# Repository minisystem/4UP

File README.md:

# SYSTEM80 4UP

4HP Eurorack Power. _Under Development_

Hardware design by minisystem: info@system80.net

# LICENSE

cc by-nc-sa
https://creativecommons.org/licenses/by-nc-sa/4.0/

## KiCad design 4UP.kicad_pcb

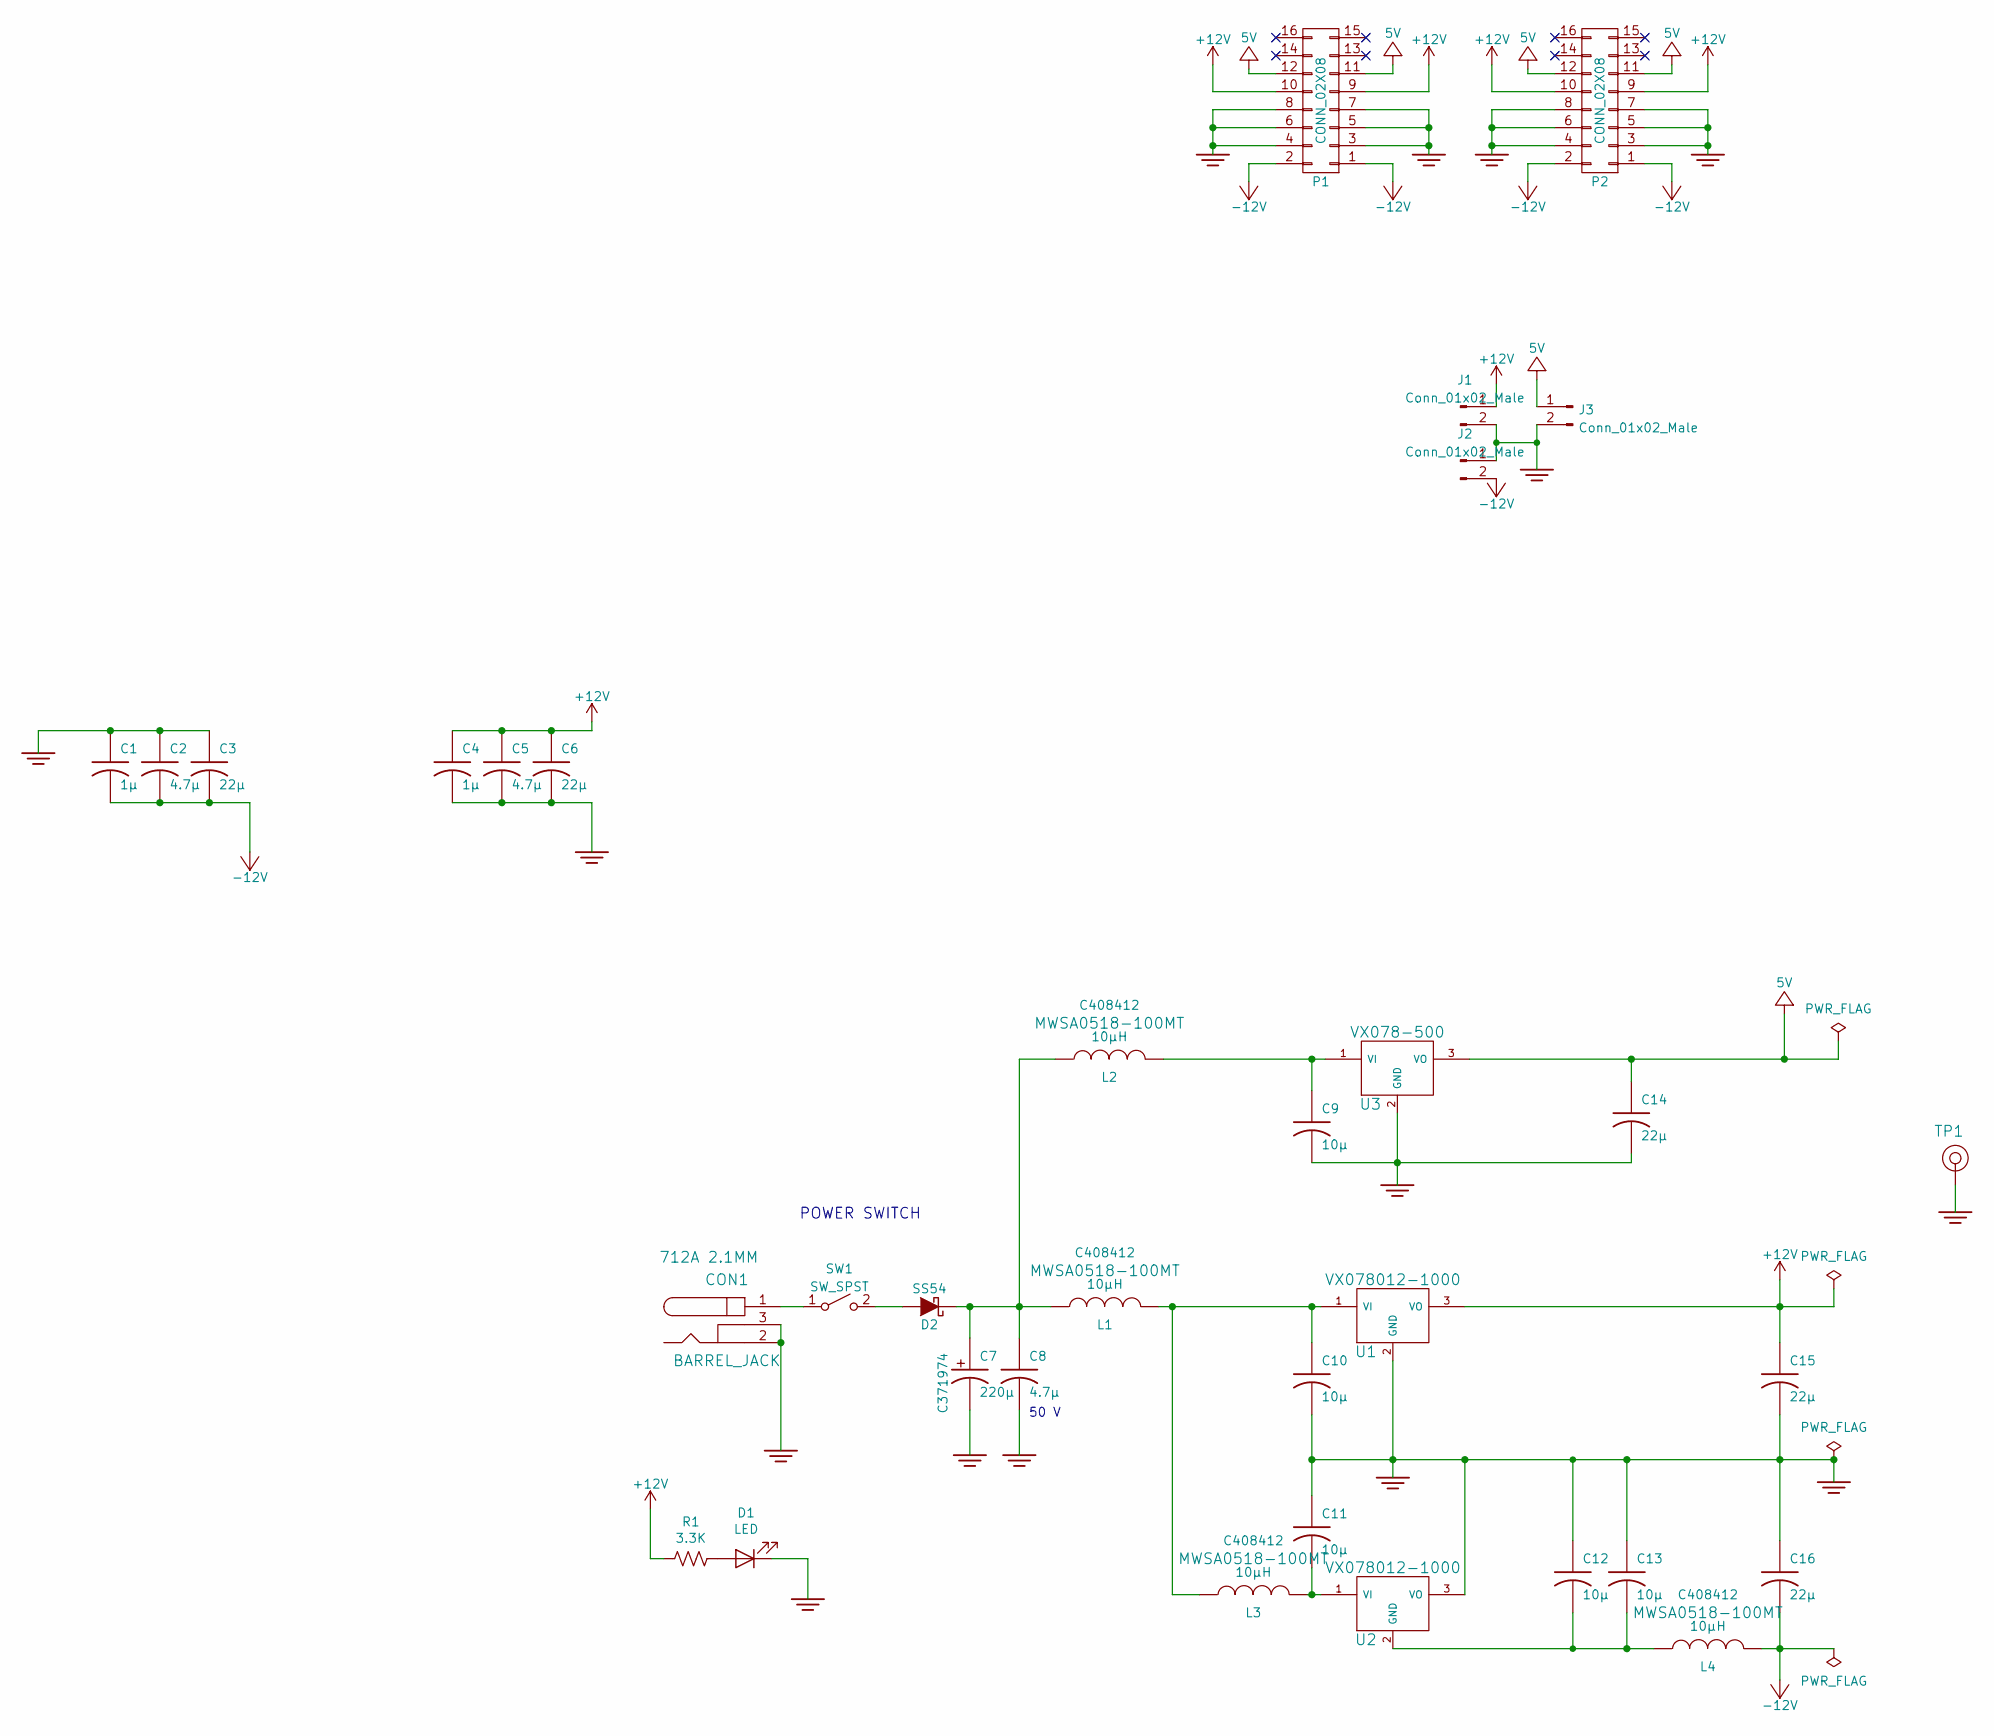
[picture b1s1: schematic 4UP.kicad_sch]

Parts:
C1, C4: 1µ; C_0603_1608Metric; LCSC C15849
C2, C5: 4.7µ; C_0805_2012Metric; LCSC C1779
C3, C6, C14, C15, C16: 22µ; C_1206_3216Metric; LCSC C12891
C7: 220µ; CP_Elec_6.3x7.7; LCSC C371974
C8: 4.7µ; C_1206_3216Metric; LCSC C132170
C9, C10, C11: 10µ; C_1206_3216Metric; LCSC C13585
C12, C13: 10µ; C_0603_1608Metric; LCSC C96446
CON1: BARREL_JACK; 712A-DC-JACK; Part Number 712A 2.1MM
D1: LED; LED_D3.0mm
D2: SS54; D_SMA; LCSC C22452
J1, J2, J3: Conn_01x02_Male; TerminalBlock_TE_282834-2_1x02_P2.54mm_Horizontal
L1, L2, L3, L4: 10µH; L_Sunlord_MWSA0518_5.4x5.2mm; Part Number MWSA0518-100MT; LCSC C408412
P1, P2: CONN_02X08; IDC-Header_2x08_P2.54mm_Vertical
R1: 3.3K; R_0603_1608Metric; LCSC C22978
SW1: SW_SPST; RA13_SW
TP1: CONN_1; TEST_POINT_LOOP_4592
U1, U2: VX078012-1000; VXO78012-1000
U3: VX078-500; CUI_VXO780XX-500

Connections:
+5V: C14.1, J3.1, P1.11, P1.12, P2.11, P2.12, U3.3 (VO)
+12V: C4.1, C5.1, C6.1, C15.1, J1.1, P1.9, P1.10, P2.9, P2.10, R1.2, U1.3 (VO)
-12V: C1.2, C2.2, C3.2, C16.2, J2.2, L4.2, P1.1, P1.2, P2.1, P2.2
GND: C1.1, C2.1, C3.1, C4.2, C5.2, C6.2, C7.2 (-), C8.2, C9.2, C10.2, C11.1, C12.1, C13.1, C14.2, C15.2, C16.1, CON1.2, CON1.3, D1.1 (K), J1.2, J2.1, J3.2, P1.3, P1.4, P1.5, P1.6, P1.7, P1.8, P2.3, P2.4, P2.5, P2.6, P2.7, P2.8, TP1.1, U1.2 (GND), U2.3 (VO), U3.2 (GND)
unnamed: C7.1 (+), C8.1, D2.1 (K), L1.1, L2.1
unnamed: C9.1, L2.2, U3.1 (VI)
unnamed: C10.1, L1.2, L3.1, U1.1 (VI)
unnamed: C11.2, L3.2, U2.1 (VI)
unnamed: C12.2, C13.2, L4.1, U2.2 (GND)
unnamed: CON1.1, SW1.1 (A)
unnamed: D1.2 (A), R1.1
unnamed: D2.2 (A), SW1.2 (B)

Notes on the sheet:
50 V
POWER SWITCH

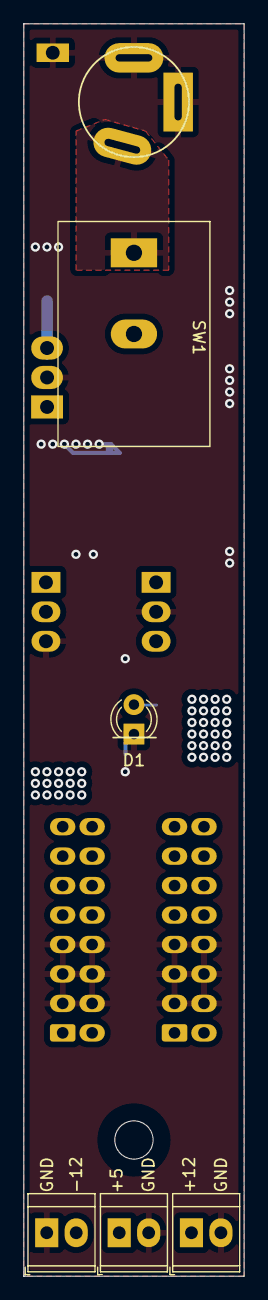
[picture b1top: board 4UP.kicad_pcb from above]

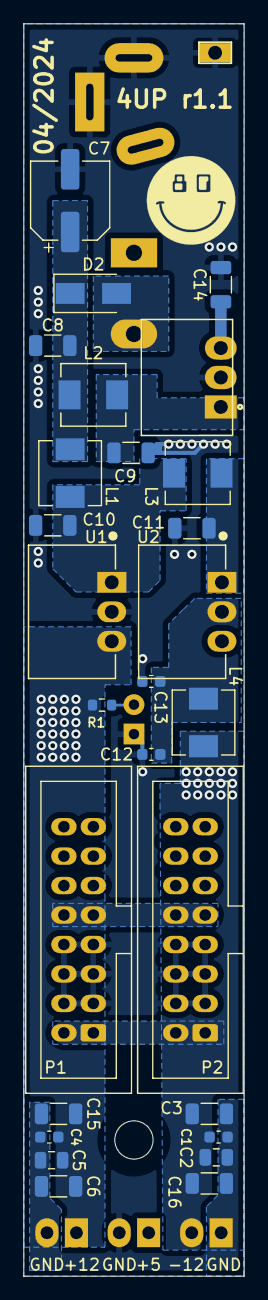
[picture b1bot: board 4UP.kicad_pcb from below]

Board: 4 copper layers, 19.0 x 108.0 mm, 34 parts (28 on the bottom side), 12 nets.

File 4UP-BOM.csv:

"Id";"Designator";"Package";"Quantity";"Designation";"Supplier and ref";
1;"REF**";"HOLE";1;"HOLE";;;
2;"D1";"LED_D3.0mm";1;"LED";;;
3;"SW1";"RA13_SW";1;"SW_SPST";;;
4;"J1,J3,J2";"TerminalBlock_TE_282834-2_1x02_P2.54mm_Horizontal";3;"Conn_01x02_Male";;;
5;"CON1";"712A-DC-JACK";1;"BARREL_JACK";;;
6;"L2,L1,L4,L3";"L_Sunlord_MWSA0518_5.4x5.2mm";4;"10µH";;;
7;"U3";"CUI_VXO780XX-500";1;"VX078-500";;;
8;"C7";"CP_Elec_6.3x7.7";1;"220µ";;;
9;"C2,C5";"C_0805_2012Metric";2;"4.7µ";;;
10;"U1,U2";"VXO78012-1000";2;"VX078012-1000";;;
11;"TP1";"TEST_POINT_LOOP_4592";1;"CONN_1";;;
12;"C6,C16,C3,C12,C14,C13,C15";"C_1206_3216Metric";7;"22µ";;;
13;"C11,C9,C10";"C_1206_3216Metric";3;"10µ";;;
14;"P1,P2";"IDC-Header_2x08_P2.54mm_Vertical";2;"CONN_02X08";;;
15;"D2";"D_SMA";1;"SS54";;;
16;"C4,C1";"C_0603_1608Metric";2;"1µ";;;
17;"R1";"R_0603_1608Metric";1;"3.3K";;;
18;"C8";"C_1206_3216Metric";1;"4.7µ";;;

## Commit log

2024-03-18 fixed interference between bulk caps and VXO PSUs
2024-03-20 ready to order
2024-04-05 ordered
